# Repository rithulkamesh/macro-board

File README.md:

# Macro Board

**This project has been archived since the work on this is just a practice to get used to software. Please do not expect this project to be continued, Thank you**

This is a programmable 6-key keyboard with a knob. Designed with [Kicad](https://www.kicad.org/) and [Fusion 360](https://www.autodesk.com/products/fusion-360).
It has the PCB Design and the 3D-Design for printing [To Be Done].

# Contributions and Credits

- [Rithul Kamesh](https://rithul.dev) - Main Programming, PCB Design
- [CrazyBlackStone](https://crazyblackstone.com) and [Hugo](https://www.hugohu.me/) for getting me started with PCB Design in [#hardware-party](https://slack.hackclub.com)

All Contributions are taken under the same license as the project i.e [GNU GPL v3](https://www.gnu.org/licenses/gpl-3.0.en.html)

# Cloning / Forking

Cloning and Forking can be done without any restrictions considering the license of the project is followed. Feel free to open a PR on something that you think might help this small hobby project.

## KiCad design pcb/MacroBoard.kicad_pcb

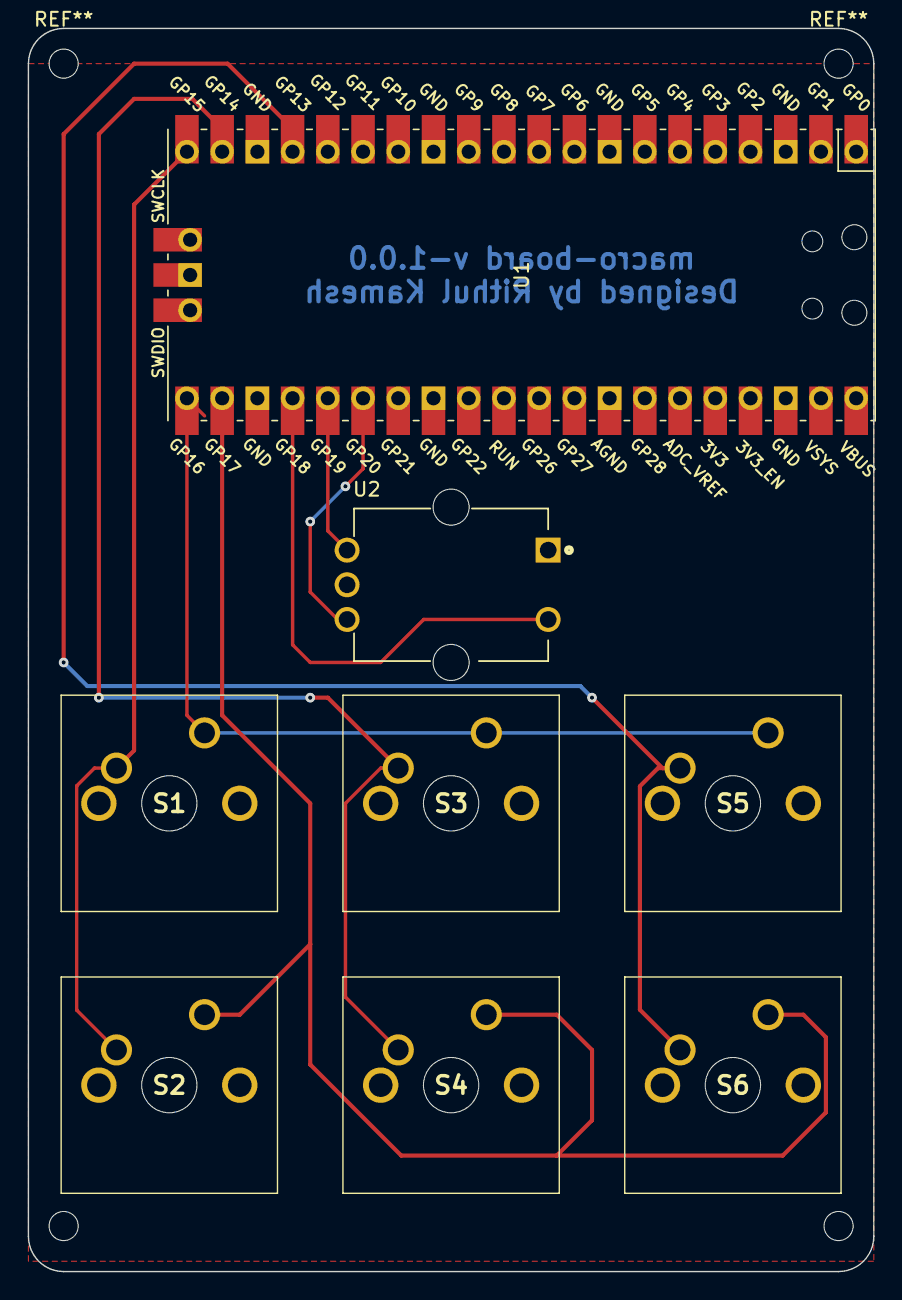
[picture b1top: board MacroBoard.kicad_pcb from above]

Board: 2 copper layers, 61.0 x 89.6 mm, 8 parts (0 on the bottom side), 9 nets.

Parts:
S1, S2, S3, S4, S5, S6: MX1A-11NW; MX1A11NW
U1: Pico; RPi_Pico_SMD_TH
U2: PEC12R-4025F-S0024; ENC_PEC12R-4025F-S0024

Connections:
Button: U1.26 (GPIO20), U2.B (CHB)
Col1: S1.1, S2.1, U1.20 (GPIO15)
Col2: S3.1, S4.1, U1.19 (GPIO14)
Col3: S5.1, S6.1, U1.17 (GPIO13)
Direction: U1.25 (GPIO19), U2.A (CHA)
Ground: U1.38 (GND), U2.1 (S1), U2.C (COM)
Row 1: S1.2, S3.2, S5.2, U1.21 (GPIO16)
Row 2: S2.2, S4.2, S6.2, U1.22 (GPIO17)
Step: U1.24 (GPIO18), U2.2 (S2)

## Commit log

2022-08-15 Hello, World!
2022-08-15 Added name in pcb
2022-08-15 Added Art + Updated README
2022-08-15 Fixing up Fumbles
2022-08-27 Archive Commit
